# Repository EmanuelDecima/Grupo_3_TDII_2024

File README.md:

# Repositorio del Grupo 3 - Tecnicas Digitales II
Aqui se subiran las Actividades de Formacion Practica (AFP) para la asignatura de Tecnicas Digitales II

## Proyecto Final - Radar Ultrasonico
El proyecto consiste en el desarrollo de un Radar Ultrasónico, diseñado para detectar objetos dentro de un rango de distancia determinado y alertar al usuario mediante mensajes a través de una pantalla LCD y un dispositivo conectado vía Bluetooth. Este sistema se basa en la medición de distancias utilizando un sensor ultrasónico HC-SR04, montado sobre un servomotor, que le permite escanear su entorno en un rango de 180°.

### Software Utilizado:
* Entorno de desarrollo: STM32CubeIDE
* Lenguaje: C (estándar GNU11)
* Bibliotecas HAL: STM32F4xx HAL Driver

### Hardware Utilizado:
* STM32F401CCU6.
* Sensor de Proximidad HCSR04.
* Servomotor SG90.
* Modulo Bluetooth HC-05.
* Pantalla LCD 16x02 con Modulo PCF85774 para la comunicacion I2C.
* Buzzer.
* 3 LEDs
* Fuente de Alimentacion 5VDC 1A

### Creamos una serie de Drivers que fueron implementados en el proyecto, Estos se encuentran en "./Drivers/API".
* **API_Delay**: Contiene las funciones para implementar delays no bloqueantes.
* **API_HC05**: Contiene las funciones para controlar el modulo Bluetooth, cuenta con funciones para enviar texto y datos numericos.
* **API_HCSR04**:Contiene las funciones para obetener los datos de proximidad medidos con el modulo HCSR04, utiliza el TIM1 CH1 en modo Input Capture para calcular el pulso que devuelve el modulo al realizar la medicion. Posee funciones adicionales para filtrar los datos y obtener mediciones estables.
* **API_LCD**:  Utilizada para controlar la pantalla LCD mediante el modulo I2C PCF8574. La librería cuenta con funciones para Inicializar el modulo con su combinacion de comandos especifica, y para enviar tanto cadenas de caracteres como datos. Tambien cuenta con las funciones adicionales necesarias para manejar la pantalla LCD como mover el cursos o limpiar la pantalla. 
* **API_MEF**: Implementacion de la maquina de estados.
* **API_Secuencias**:  Posee dos funciones, la secuencia de inicio y la secuencia que sigue el dispositivo cuando la alarma esta activada.
* **API_Servo**: Contiene la inicializacion del TIM3 CH1 para el uso de señales PWM que permiten controlar el servomotor y otra funcion que realiza el calculo del ancho de pulso necesario para establecer un angulo determinado en el servomotor.

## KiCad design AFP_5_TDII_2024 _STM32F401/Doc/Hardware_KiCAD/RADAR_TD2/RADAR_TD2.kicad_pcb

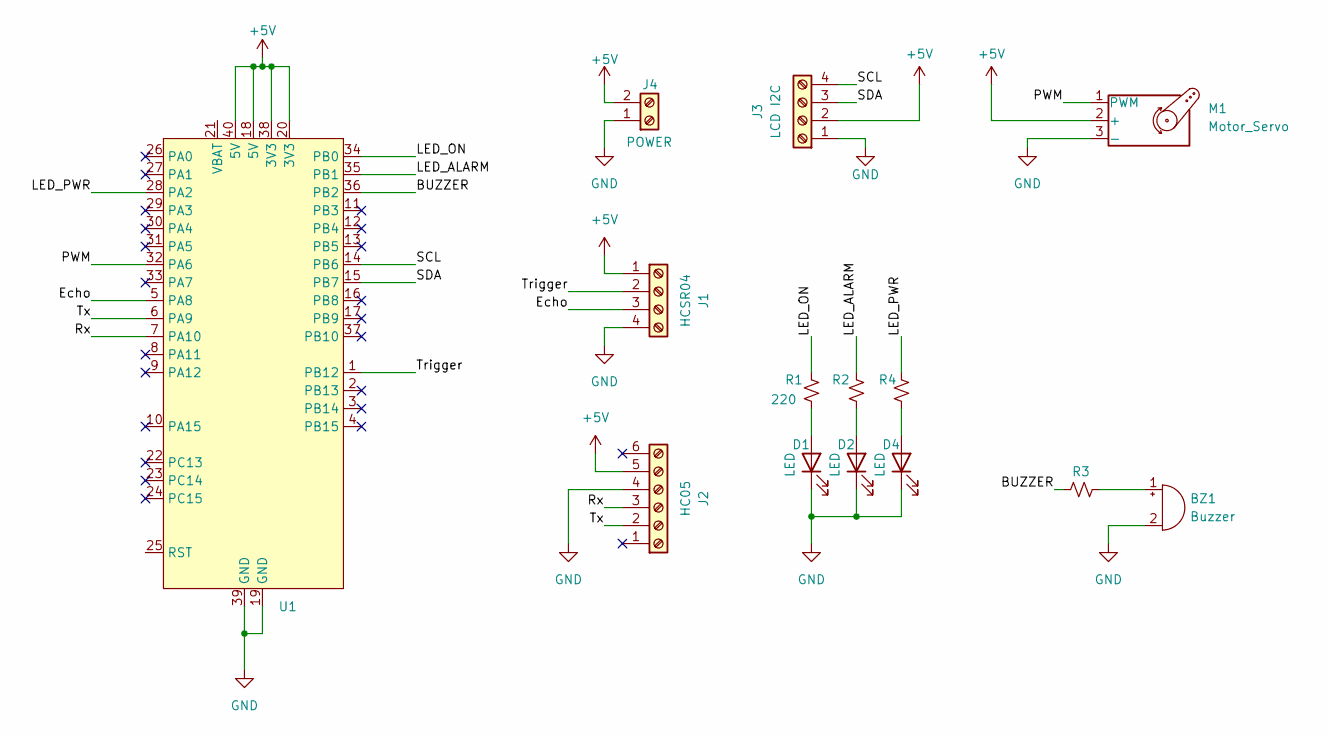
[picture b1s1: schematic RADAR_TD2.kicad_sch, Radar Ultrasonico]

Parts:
BZ1: Buzzer; Buzzer_12x9.5RM7.6
D1, D2, D4: LED; LED_D5.0mm
J1: HCSR04; PinHeader_1x04_P2.54mm_Vertical
J2: HC05; PinSocket_1x06_P2.54mm_Vertical
J3: LCD I2C; PinSocket_1x04_P2.54mm_Vertical
J4: POWER; TerminalBlock_Phoenix_MKDS-1,5-2-5.08_1x02_P5.08mm_Horizont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
M1: Motor_Servo; PinHeader_1x03_P2.54mm_Vertical
R1, R2, R3, R4: 220; R_Axial_DIN0204_L3.6mm_D1.6mm_P7.62mm_Horizontal
U1: STM32BlackPill

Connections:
+5V: J1.1, J2.5, J3.2, J4.2, M1.2 (+), U1.18 (5V), U1.20 (3V3), U1.38 (3V3), U1.40 (5V)
/BUZZER: R3.2, U1.36 (PB2)
/Echo: J1.3, U1.5 (PA8)
/LED_ALARM: R2.2, U1.35 (PB1)
/LED_ON: R1.2, U1.34 (PB0)
/LED_PWR: R4.2, U1.28 (PA2)
/PWM: M1.1 (PWM), U1.32 (PA6)
/Rx: J2.3, U1.7 (PA10)
/SCL: J3.4, U1.14 (PB6)
/SDA: J3.3, U1.15 (PB7)
/Trigger: J1.2, U1.1 (PB12)
/Tx: J2.2, U1.6 (PA9)
GND: BZ1.2 (-), D1.1 (K), D2.1 (K), D4.1 (K), J1.4, J2.4, J3.1, J4.1, M1.3 (-), U1.19 (GND), U1.39 (GND)
unnamed: BZ1.1 (+), R3.1
unnamed: D1.2 (A), R1.1
unnamed: D2.2 (A), R2.1
unnamed: D4.2 (A), R4.1

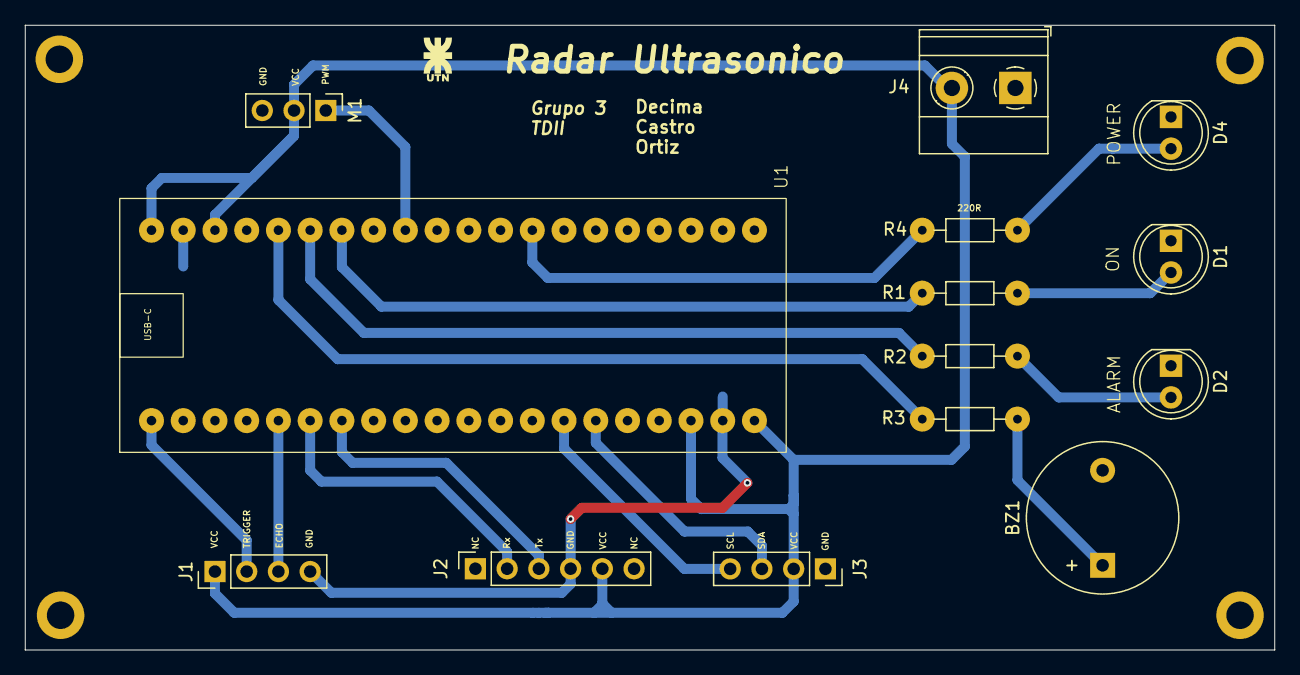
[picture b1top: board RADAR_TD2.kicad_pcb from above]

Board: 2 copper layers, 100.0 x 50.0 mm, 14 parts (0 on the bottom side), 17 nets.

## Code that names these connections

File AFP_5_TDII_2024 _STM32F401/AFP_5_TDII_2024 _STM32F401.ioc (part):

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Mcu.Name=STM32F401C(B-C)Ux
Mcu.Package=UFQFPN48
Mcu.UserName=STM32F401CCUx
PA10.Mode=Asynchronous
PA10.Signal=USART1_RX
PA2.GPIOParameters=PinState,GPIO_Label
PA2.GPIO_Label=LED_PWR
PA2.PinState=GPIO_PIN_SET
PA2.Signal=GPIO_Output
PA6.Signal=S_TIM3_CH1
PA8.Signal=S_TIM1_CH1
PA9.Mode=Asynchronous
PA9.Signal=USART1_TX
PB0.GPIOParameters=GPIO_Label
PB0.GPIO_Label=LED_ON
PB0.Signal=GPIO_Output
PB1.GPIOParameters=GPIO_Label
PB1.GPIO_Label=LED_ALARM
PB1.Signal=GPIO_Output
PB12.GPIOParameters=GPIO_Label
PB12.GPIO_Label=Trigger
PB12.Signal=GPIO_Output
PB2.GPIOParameters=GPIO_Label
PB2.GPIO_Label=BUZZER
PB2.Signal=GPIO_Output
PB6.Mode=I2C
PB6.Signal=I2C1_SCL
PB7.Mode=I2C
PB7.Signal=I2C1_SDA
PC13-ANTI_TAMP.GPIOParameters=GPIO_Label
PC13-ANTI_TAMP.GPIO_Label=LED0
PC13-ANTI_TAMP.Signal=GPIO_Output
PC14-OSC32_IN.Mode=LSE-External-Clock-Source
PC14-OSC32_IN.Signal=RCC_OSC32_IN
PC15-OSC32_OUT.Mode=LSE-External-Clock-Source
PC15-OSC32_OUT.Signal=RCC_OSC32_OUT
PH0\ -\ OSC_IN.Mode=HSE-External-Clock-Source
PH0\ -\ OSC_IN.Signal=RCC_OSC_IN
PH1\ -\ OSC_OUT.Mode=HSE-External-Clock-Source
PH1\ -\ OSC_OUT.Signal=RCC_OSC_OUT
RCC.HSE_VALUE=25000000
RCC.SYSCLKFreq_VALUE=84000000
RCC.SYSCLKSource=RCC_SYSCLKSOURCE_PLLCLK
board=custom

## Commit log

2024-08-08 Proyecto iniciado, IOC configurado
2024-08-08 Secuencia de luces
2024-08-08 APP1.2 Init
2024-08-08 APP1.2: Funcion secuencia1
2024-08-08 APP1.2: Funcion secuencia2
2024-08-08 Bug Solucionado
2024-08-08 APP1.2: Funcionalidad Boton
2024-08-09 App 1.3: Init, secuencia 1
2024-08-09 App 1.3: secuencia 2
2024-08-09 App 1.4: secuencia 3
2024-08-09 App 1.3: secuencia 4
2024-08-09 App 1.3: Funcionalidad Boton
2024-08-09 App 1.4: Proyecto Iniciado, IOC configurado
2024-08-09 App 1.4: Secuencia
2024-09-25 Creacion de la Libreria API_GPIO->Implementada en APP1.2
2024-10-18 Implementacion de libreria API_GPIO en APP1.3: Decima, Emanuel
2024-10-18 Implementacion de libreria API_GPIO en APP1.1: ORTIZ, AGUSTIN
2024-10-18 Implementacion de libreria API_GPIO en APP1.4: Castro, Oscar Martin
2024-10-27 Reorganizacion de Directorios y Carpetas
2024-10-31 agrego informes de cada actividad
2024-10-31 Solucion Bug App 1.2
2024-10-31 Solucion Bug App 2.2
2024-11-03 Solucion Warning Libreria API_GPIO
2024-11-03 Creacion de la libreria API_Delay para el manejo de funciones no bloqueantes
2024-11-03 App 3.3 Secuencia 1
2024-11-03 App 3.3 Secuencia 2
2024-11-03 App 3.3 Secuencia 3
2024-11-03 App 3.3 Secuencia 4
2024-11-03 App 3.3 Funciona Correctamente
2024-11-04 Agrego comentarios y explicacion en App 3.3
2024-11-06 Creacion de la libreria API_debounce, Implementada en App 4.2
2024-11-13 App 3.1
2024-11-13 App 3.2
2024-11-13 App 3.4
2024-11-13 App 4.3
2024-11-13 App 4.4
2024-12-02 Agrego informe AFP3 y AFP4
2025-02-11 Se inicia el proyecto final
2025-02-12 Agrego librerias RADAR_GPIO y RADAR_Delay
2025-02-14 Reconfiguracion del IOC y Agrego Libreria RADAR_HC05 para el Bluetooth
2025-02-14 Agrego libreria MEF
2025-02-17 Agrego libreria RADAR_HCSR04 para la medicion de distancia
2025-02-17 MEF adaptada a la nueva libreria HCSR04
2025-02-17 Documentacion: Pinout
2025-02-21 Agrego Libreria RADAR_Servo
2025-02-22 Agrego librerias de LCD
2025-02-23 Inicio Proyecto en Placa STM32F401CCU6
2025-02-23 Organizacion y Comentarios en las librerias
2025-02-23 Funciona Correctamente V1.0
2025-02-25 Modificacion en el Pinout
2025-02-25 Agrego Proyecto KiCAD, Esquematico y Archivos de Impresion
2025-02-26 Warnings Solucionados y Refactorizacion del Codigo
2025-02-26 Elimino el proyecto inicial en STM32F429ZI
2025-02-26 Actualizo Documentacion del Pinout
2025-02-27 Solucion de Bugs
2025-02-27 Agrego Comentarios en Secuencia_Inicio
2025-02-28 Cambios menores en la rutina de error
2025-02-28 Bloqueo de Salidas no utilizadas
2025-02-28 Agrego informe y presentacion del Proyecto Final
2025-03-02 Calibracion del sensor HCSR04
